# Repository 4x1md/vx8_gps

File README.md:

# DIY GPS Module for Yaesu VX-8DR/VX-8DE Handheld Transceiver
GPS module for Yaesu VX-8DR/DE handheld transceivers with ublox NEO-6M chip and Arduino Nano by Dmitry Melnichansky 4Z7DTF (~~4X5DM since June 2016~~ 4X1MD since July 24, 2017).

## Overview

When I was buying my Yaesu VX-8DE, I knew that I wasn't going to buy the original Yaesu FGPS2 module. There is very little APRS coverage in Israel and APRS in general seemed quite useless to me. The unreasonably high price of the original module didn't make me want to try it either.

After receiving far APRS stations during a strong tropo over the Mediterranean I thought it would be nice to transmit some data. I started investigating how GPS transmits data and discovered the NMEA protocol I had never encountered before. My first source of information was the article [Reverse Engineering the Yaesu VX-8DR GPS Interface](http://lingnik.com/2013/02/09/reverse-engineering-yaesu-vx-8dr-gps-interface.html) by Taylor J Meek KG7BBG.

I started from writing a Python program which was sending NMEA sentences to the transceiver. After some research I discovered the required message format and wrote a program which drew flowers on APRS map.

Later, [David Fannin's project](https://github.com/dfannin/arduino-vx8r-gps) inspired me to build my own GPS module. Thanks to his project I found out the ublox NEO-6M chip and a simple search on AliExpress showed that a ready module can be puchased for $10-20.

I wrote my own software which isn't based on David Fannin's code. I started it as Arduino project but after finding out that the standard Arduino Serial library doesn't support interrupt driven writing and reading I decided to write it in pure C. After small changes the C code can be compiled in Arduino environment. The Arduino code is located in [/arduino/vx8_gps_16mhz folder](https://github.com/4x5dm/vx8_gps/blob/master/arduino/vx8_gps_16mhz) of this repository.

I tried to document this project as much as possible and I hope it will be interesting and useful for other radio amateurs.

## Yaesu VX-8DR/DE and NMEA protocol
The NMEA protocol is implemented in the VX-8 in a non-standard way. There are two main issues with it: serial port parameters and NMEA sentence format. There is also a data validation issue which is very interesting but less important in this case.

### Port parameters: baud rate and logic levels
The original Yaesu FGPS2 module transmits at 9600 bps instead of the standard 4800 bps and uses 3.3V logic level instead of the standard 5V. This isn't a big issue because there are GPS modules which can be configured to transmit at 9600 bps and logic levels can be converted. The GY-GPS6MV2 module came already pre-configured to 9600 bps rate. The ublox NEO-6M chip used in this module has maximum supply voltage of 3.6V. As we see there are no electrical compatibility issues at all.
### NMEA sentence format: field lengths
VX-8 requires all the fields of the NMEA sentence to be padded to the maximum possible number of symbols while regular NMEA standart allows fields to be empty. It means that if there is no GPS fix, typical GGA message will have the following form:
```
$GPGGA,074222.000,,,,,0,00,99.9,,,,,,0000*6E
```
The radio won't be able to process this message and we'll see gibberish on the display. A correct sentence for this transceiver should have the following format:
```
$GPGGA,200124.000,0000.0000,N,00000.0000,E,0,00,00.0,00000.0,M,0000.0,M,000.0,0000*46
```
Sending a sentence with empty fields will result in gibberish on the GPS screen of VX-8. Here is what we'll get.

Allthough the sentence accords with the standard, the transceiver isn't able to process it correctly.

Actually setting number of sybols in each field is what all this project is about! If the second issue didn't exist we could connect the ublox NEO-6M chip based module directly to the transceiver.

### NMEA data validation
Here the things get even more interesting. Yaesu VX-8 does no validation on the NMEA data. When I say no validation, I mean **no validation at all**! Let's look at the following NMEA sentence.
```
$GPGGA,999999.000,73DE.0000,!,Z7DTF.NOPQ,4,1,04
```
The time in the first field is invalid, the latitude and longitude fields have letters instead of numbers, the North/South and East/West fields have invalid characters as well. The checksum is missing. Should it be thrown away by the receiving device? Yes, sure! But let's see how VX-8 will respond!

Have you ever thought about writing some text on the display of your VX-8? Or maybe about setting the time to 89:91:75? Now you know how to do it!

Let's try one more example where there will be no numbers in latitude and longitude fields.
```
$GPGGA,999999.000,ello.ABCD,H,itHub.ABCD,G,1,04
```
And the output is:

Note that last two fields of our so called NMEA sentence mean that there was a valid GPS fix and that it was acquired from 4 satellites. This is exactly what we see on the display: satellites icon with number 4 under it.  This is enough for the transceiver to enable APRS beacon transmission. If you press the internet (TX PO) key these coordinates will be transmitted. Obviously, APRS site will mark such packet as invalid.

When I told you that there is no data validation I really meant no validation at all! You don't even have to add checksum as it will be completely ignored by the radio.

If you want to try it your self you'll need a standard programming cable (original or one from AliExpress) and a terminal program. I used [PuTTY](http://www.putty.org/). Open a new session, choose the correct serial port, set it to 9600 8N1 and you are ready to go. Right mouse click in the terminal window pastes the message from the clipboard. After pasting your message press CTRL+M and then CTRL+J. It will send the CR and LF (ASCII 13 and 10) symbols which mark the end of NMEA sentence.

## Hardware

The hardware is quite simple. GY-GPS6MV2 GPS module transmits its data to the Arduino which does necessary processing and sends it to the transceiver. Allthough the communication between the original Yaesu FGPS2 module and the radio is bi-directional, in my project I decided to make it unidirectional from GPS to radio. Not only is the bi-directional communication useless in this case but also requires one more serial port. This configuration uses only one serial port to communicate with both devices.

Important! The serial port on the Arduino board is also used for programming the device. Leaving the GPS connected to the serial RX pin will cause a conflict and make uploading the firmware impossible. That's why there is a switch which disconnects GPS output from serial input.

On the contrary, using USB serial when the transceiver is connected not only is possible but also is recommended for debugging purposes. You can use any terminal program to monitor Arduino's output even when the radio is connected.

Voltage divider formed by 240 Ohm and 470 Ohm resistors converts the logic levels from 5V used by Arduino to 3.3V required by the transceiver. Two two-color LEDs are used for indication. The left one blinks red if a GGA message was rejected and green if it was sent to the radio. The right one does the same for RMC messages.

All the setup is very similar to [David Fannin's GPS project](https://github.com/dfannin/arduino-vx8r-gps). Main difference is that his project implements bi-directional communication using software serial port emulation for the second port.

The GY-GPS6MV2 GPS recevier and the Arduino Nano clone were both purchases on AliExpress for less than $15.

## Software

To be completed...

## Development history

### First protoype: Arduino Nano and u-blox NEO-6M

The first version was built with readily available modules on a prototype PCB.

### PCB v1.0

The first prototype was built on a dedicated PCB with a standalone ATmega328P-20PU microcontroller in 28 pin DIP package. The PCB was produced at home.

Refer to [prototype_v1.0.md](https://github.com/4x5dm/vx8_gps/blob/master/docs/prototype_v1.0.md) for details.

### PCB v2.0

This version has a USB-to-UART IC which allows the GPS to be used as a programming cable. It was designed as a two-side PCB with SMD parts. Allthough I developed the schematics and the PCB, this version was never built.

The circuit diagram of this version can be found [here](https://raw.githubusercontent.com/4x5dm/vx8_gps/master/docs/images/vx8_gps_prototype_v2.0_schematic.png). Design files are located [here](https://github.com/4x1md/vx8_gps/tree/master/pcbs/vx8_gps_prototype_v2.0).

### PCB v3.0

This version was built on a two-layer PCB. Most parts including ATmega328P microcontroller and the GPS module are SMD. The size of this PCB is 43.5x43.5mm and it was designed to fit a small plastic enclosure box.

Refer to [prototype_v3.0.md](https://github.com/4x5dm/vx8_gps/blob/master/docs/prototype_v3.0.md) for details.

## Field tests

The unit was tested in trains. Videos from the tests are available.

1. [Test 1: Herzliya station](http://www.youtube.com/watch?v=POHEborbWdw)
2. [Test 2: Kiryat Gat station](https://www.youtube.com/watch?v=_s_EKdAwrpI)

## Plans for future development

1. [x] ~~Running all the system at 3.3V.~~ See [prototype_v1.0.md](https://github.com/4x5dm/vx8_gps/blob/master/docs/prototype_v1.0.md) for details.
2. [x] ~~Reducing the microcontroller speed to 8MHz or even lower.~~ See [Release v1.0](https://github.com/4x5dm/vx8_gps/releases/tag/v1.0) ([commit 9e8273a](https://github.com/4x5dm/vx8_gps/commit/9e8273abed9b53197791b6e432649a282e6ca909)) .
3. [ ] Adding a rechargeable battery and making the device USB chargeable.
4. [x] ~~Building the project on a PCB instead of using ready modules.~~
5. [x] ~~Assembling the device in one enclosure box.~~
6. [ ] Making the module compatible with Nikon DSLRs.

Optional/questionable features:

1. [ ] USB serial chip to use the device as a programming cable.
2. [ ] microSD card slot and keeping logs of the tracks.
3. [ ] LCD display for displaying current GPS data.

## Links
1. [Reverse Engineering the Yaesu VX-8DR GPS Interface](http://lingnik.com/2013/02/09/reverse-engineering-yaesu-vx-8dr-gps-interface.html)
2. [FGPS2 data samples (VX-8R Yahoo Group)](https://groups.yahoo.com/neo/groups/VX_8R/conversations/topics/7719)
3. [David Fannin's Yaesu VX-8R Handheld Transmitter-compatible GPS](https://github.com/dfannin/arduino-vx8r-gps)
4. [NMEA to Yaesu VX-8 by G7UHN](http://alloutput.com/amateur-radio/nmea-to-yaesu-vx-8/)
5. [VX-8DR and GPS by VK3YY](https://vk3yy.wordpress.com/2015/07/24/vx-8dr-and-gps/)
6. [GPS - NMEA sentence information](http://aprs.gids.nl/nmea/)
7. [MTK NMEA checksum calculator](http://www.hhhh.org/wiml/proj/nmeaxor.html)
8. [avr-libc 2.0.0: <avr/interrupt.h>: Interrupts](http://www.nongnu.org/avr-libc/user-manual/group__avr__interrupts.html)

## Questions? Suggestions?
You are more than welcome to contact me with any questions, suggestions or propositions regarding this project. You can:

1. Visit [my QRZ.COM page](https://www.qrz.com/db/4X5DM)
2. Visit [my Facebook profile](https://www.facebook.com/Dima.Meln)
3. Write me an email to iosaaris =at= gmail dot com

## How to Support or Say Thanks

If you like this project, or found here some useful information and want to say thanks, or encourage me to do more, you can buy me a coffee!

You can aslo make a donation with PayPal:

---

**73 de 4X1MD ex 4X5DM ex 4Z7DTF**

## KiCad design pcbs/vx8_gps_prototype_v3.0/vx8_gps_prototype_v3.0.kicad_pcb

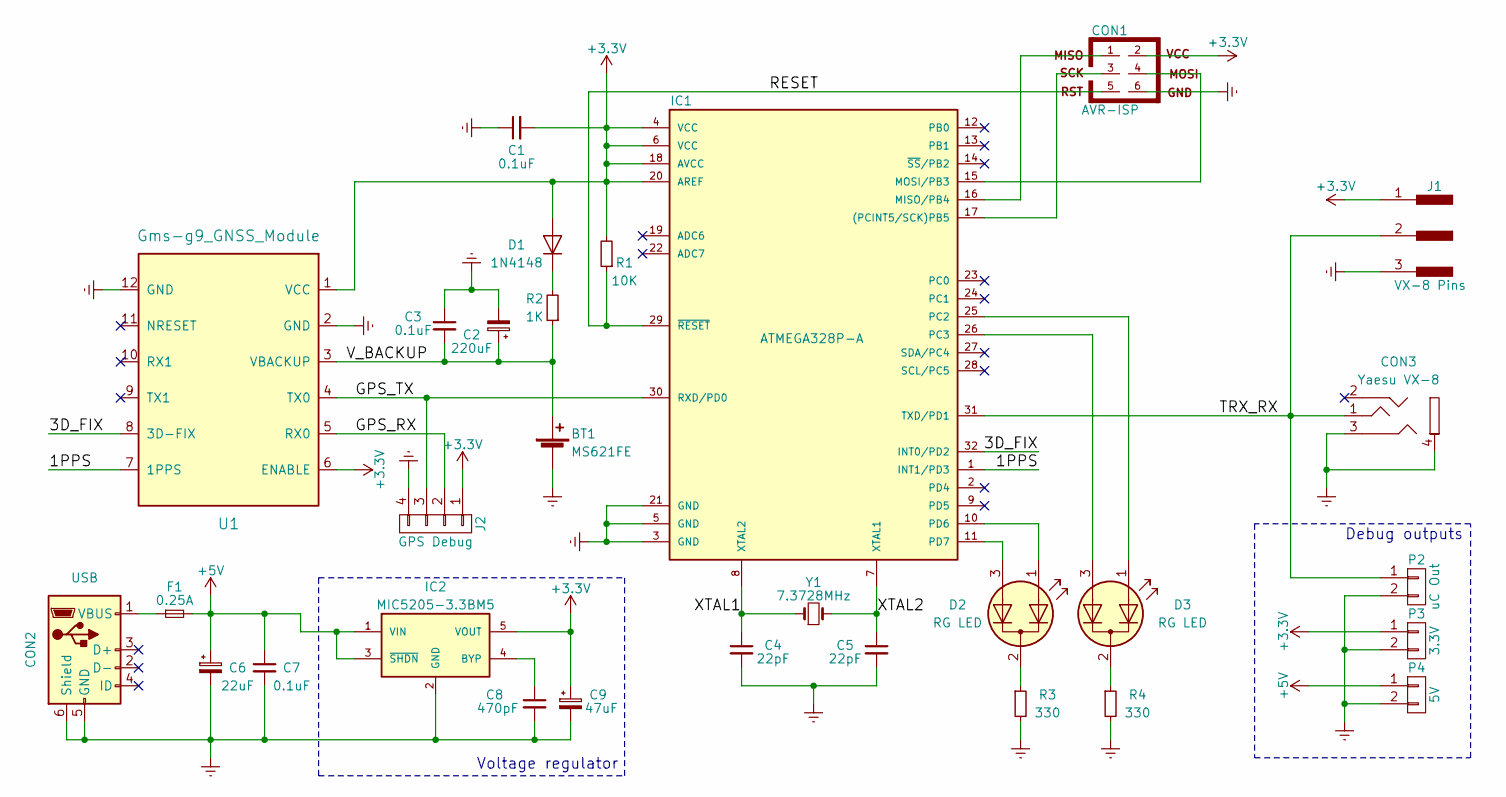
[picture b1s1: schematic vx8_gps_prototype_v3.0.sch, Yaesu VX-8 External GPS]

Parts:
BT1: MS621FE; Seiko_MS621FE-FL11E_Battery
C1, C3, C7: 0.1uF; C_1206
C2: 220uF; CP_Elec_5x5.3
C4, C5: 22pF; C_1206
C6: 22uF; CP_Elec_4x4.5
C8: 470pF; C_1206
C9: 47uF; CP_Elec_4x4.5
CON1: AVR-ISP; Pin_Header_Straight_2x03_Pitch2.54mm
CON2: USB; USB_Mini-B
CON3: Yaesu VX-8; PJ320D_3.5mm_Jack_Short
D1: 1N4148; D_MiniMELF_Standard
D2, D3: RG LED; LED_D3.0mm-3
F1: 0.25A; Fuse_SMD1206_Wave
IC1: ATMEGA328P-A; TQFP-32_7x7mm_Pitch0.8mm
IC2: MIC5205-3.3BM5; SOT-23-5
J1: VX-8 Pins; Connection_Pads_03
J2: GPS Debug; Pin_Header_Straight_1x04_Pitch2.54mm
P2: uC Out; Pin_Header_Straight_1x02_Pitch2.54mm
P3: 3.3V; Pin_Header_Straight_1x02_Pitch2.54mm
P4: 5V; Pin_Header_Straight_1x02_Pitch2.54mm
R1: 10K; R_1206
R2: 1K; R_1206
R3, R4: 330; R_1206
U1: Gms-g9_GNSS_Module
Y1: 7.3728MHz; Crystal_HC49-4H_Vertical

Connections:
+3V3: C1.2, C9.1, CON1.2, D1.2 (A), IC1.4 (VCC), IC1.6 (VCC), IC1.18 (AVCC), IC1.20 (AREF), IC2.5 (VOUT), J1.1, J2.1, P3.1, R1.2, U1.1 (VCC), U1.6 (ENABLE)
+5V: C6.1, C7.1, F1.2, IC2.1 (VIN), IC2.3 (~SHDN~), P4.1
/1PPS: IC1.1 (INT1/PD3), U1.7 (1PPS)
/3D_FIX: IC1.32 (INT0/PD2), U1.8 (3D-FIX)
/GPS_RX: J2.2, U1.5 (RX0)
/GPS_TX: IC1.30 (RXD/PD0), J2.3, U1.4 (TX0)
/RESET: CON1.5, IC1.29 (~RESET~), R1.1
/TRX_RX: CON3.1 (R), IC1.31 (TXD/PD1), J1.2, P2.1
/V_BACKUP: BT1.1 (+), C2.1, C3.2, R2.1, U1.3 (VBACKUP)
/XTAL1: C4.1, IC1.8 (XTAL2), Y1.1
/XTAL2: C5.1, IC1.7 (XTAL1), Y1.2
GNDREF: BT1.2 (-), C1.1, C2.2, C3.1, C4.2, C5.2, C6.2, C7.2, C8.2, C9.2, CON1.6, CON2.5 (GND), CON2.6 (Shield), CON3.3 (GND), CON3.4 (Mic), IC1.3 (GND), IC1.5 (GND), IC1.21 (GND), IC2.2 (GND), J1.3, J2.4, P2.2, P3.2, P4.2, R3.2, R4.2, U1.2 (GND), U1.12 (GND)
unnamed: C8.1, IC2.4 (BYP)
unnamed: CON1.1, IC1.16 (MISO/PB4)
unnamed: CON1.3, IC1.17 ((PCINT5/SCK)PB5)
unnamed: CON1.4, IC1.15 (MOSI/PB3)
unnamed: CON2.1 (VBUS), F1.1
unnamed: D1.1 (K), R2.2
unnamed: D2.1 (A1), IC1.10 (PD6)
unnamed: D2.2 (K), R3.1
unnamed: D2.3 (A2), IC1.11 (PD7)
unnamed: D3.1 (A1), IC1.25 (PC2)
unnamed: D3.2 (K), R4.1
unnamed: D3.3 (A2), IC1.26 (PC3)

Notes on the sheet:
Debug outputs
Voltage regulator

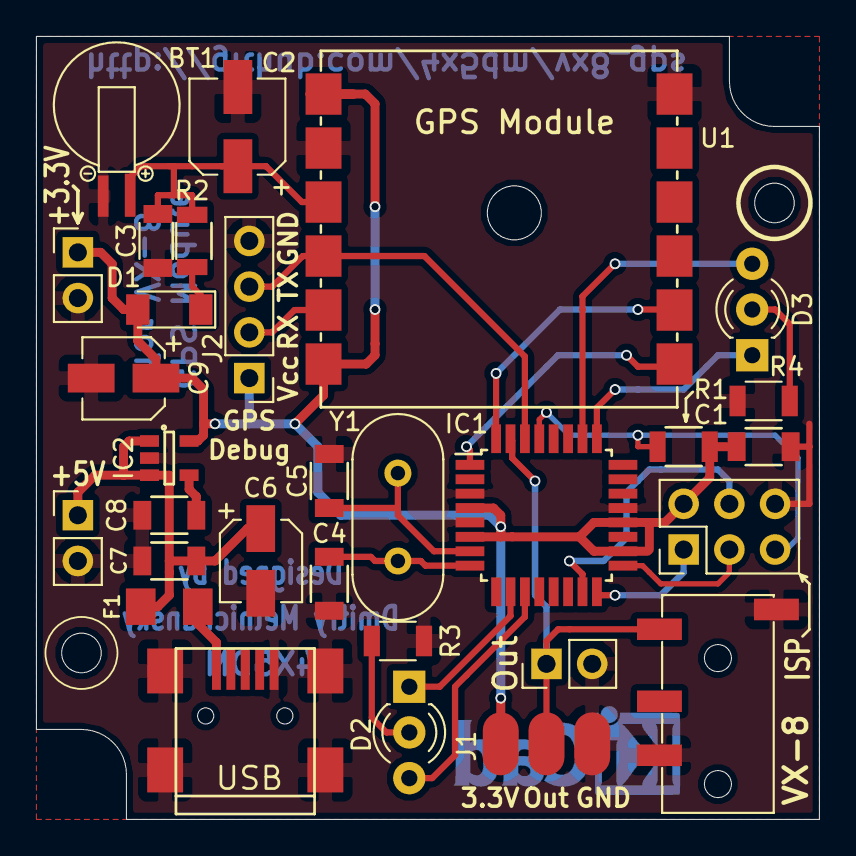
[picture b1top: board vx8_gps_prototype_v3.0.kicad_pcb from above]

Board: 2 copper layers, 43.5 x 43.5 mm, 32 parts (0 on the bottom side), 24 nets.

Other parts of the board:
MH1, MH2: M2; MountingHole_2.2mm_M2

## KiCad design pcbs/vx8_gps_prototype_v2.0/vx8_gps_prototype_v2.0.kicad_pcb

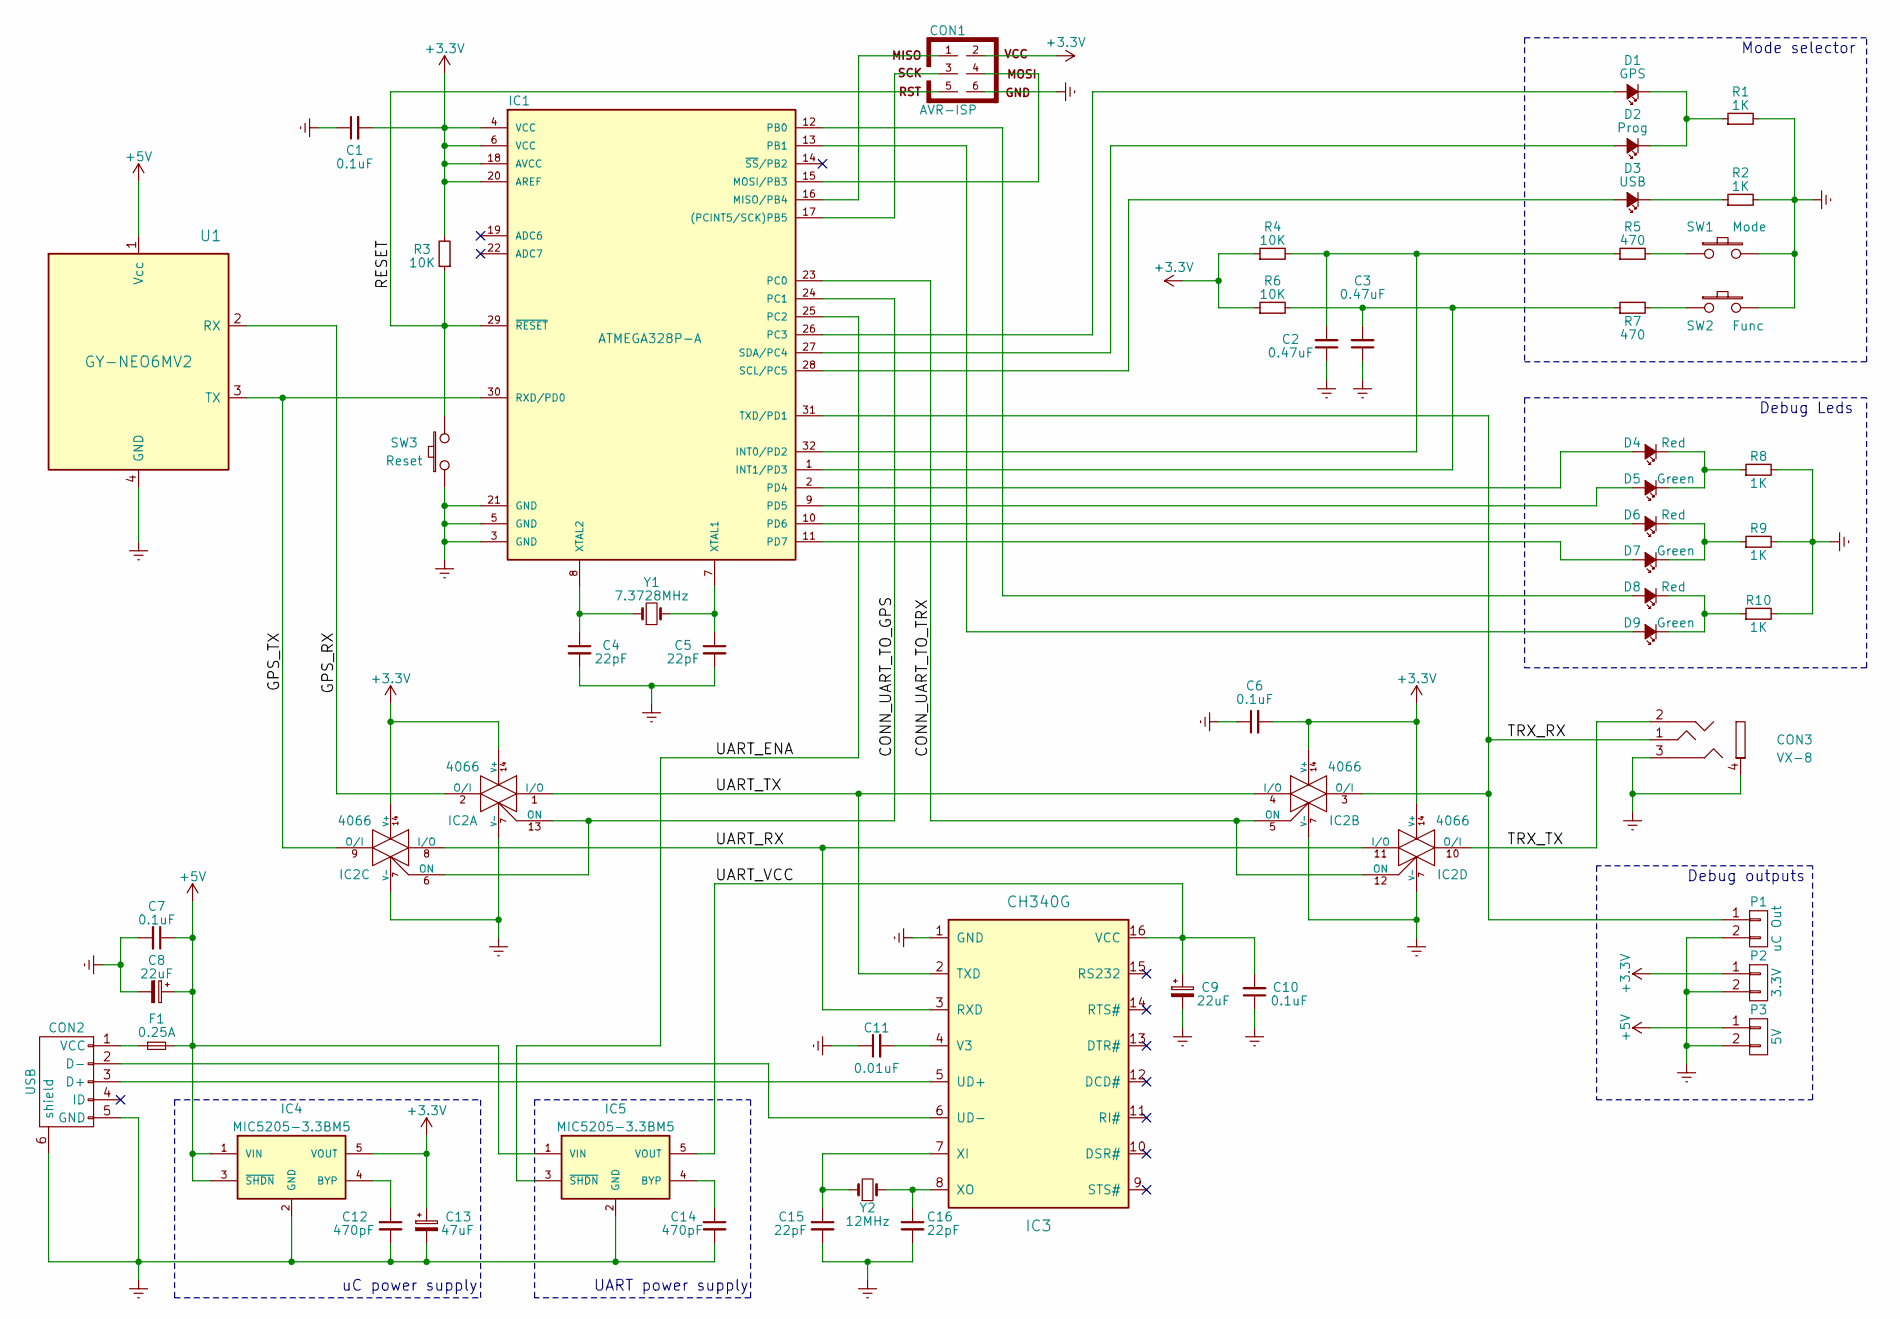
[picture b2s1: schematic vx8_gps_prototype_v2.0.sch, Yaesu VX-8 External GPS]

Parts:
C1, C6, C7, C10: 0.1uF; C_1206
C2, C3: 0.47uF; C_1206
C4, C5, C15, C16: 22pF; C_1206
C8, C9: 22uF; C_Radial_D5_L6_P2.5
C11: 0.01uF; C_1206
C12, C14: 470pF; C_1206
C13: 47uF; C_Radial_D5_L6_P2.5
CON1: AVR-ISP; Pin_Header_Straight_2x03
CON2: USB; USB_Mini-B
CON3: VX-8; PJ320D_3.5mm_Jack
D1: GPS; LED_1206
D2: Prog; LED_1206
D3: USB; LED_1206
D4, D6, D8: Red; LED_1206
D5, D7, D9: Green; LED_1206
F1: 0.25A; Fuse_SMD1206_Wave
IC1: ATMEGA328P-A; TQFP-32_7x7mm_Pitch0.8mm
IC2: 4066; SOIC-14_3.9x8.7mm_Pitch1.27mm
IC3: CH340G; SOIC-16_3.9x9.9mm_Pitch1.27mm
IC4, IC5: MIC5205-3.3BM5; SOT-23-5
P1: uC Out; Pin_Header_Straight_1x02_Pitch2.54mm
P2: 3.3V; Pin_Header_Straight_1x02_Pitch2.54mm
P3: 5V; Pin_Header_Straight_1x02_Pitch2.54mm
R1, R2, R8, R9, R10: 1K; R_1206
R3, R4, R6: 10K; R_1206
R5, R7: 470; R_1206
SW1: Mode; SW_SPST_PTS645
SW2: Func; SW_SPST_PTS645
SW3: Reset; SW_SPST_B3U-1000P
U1: GY-NEO6MV2; GY-NEO6MV2_GPS
Y1: 7.3728MHz; HC-49V
Y2: 12MHz; Q_49U3HMS

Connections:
+3V3: C1.2, C6.2, C13.1, CON1.2, IC1.4 (VCC), IC1.6 (VCC), IC1.18 (AVCC), IC1.20 (AREF), IC2.14 (V+), IC4.5 (VOUT), P2.1, R3.2, R4.1, R6.1
+5V: C7.1, C8.1, F1.2, IC4.1 (VIN), IC4.3 (~SHDN~), IC5.1 (VIN), P3.1, U1.1 (Vcc)
/CONN_UART_TO_GPS: IC1.24 (PC1), IC2.6 (ON), IC2.13 (ON)
/CONN_UART_TO_TRX: IC1.23 (PC0), IC2.5 (ON), IC2.12 (ON)
/GPS_RX: IC2.2 (O/I), U1.2 (RX)
/GPS_TX: IC1.30 (RXD/PD0), IC2.9 (O/I), U1.3 (TX)
/RESET: CON1.5, IC1.29 (~RESET~), R3.1, SW3.2
/TRX_RX: CON3.1 (R), IC1.31 (TXD/PD1), IC2.3 (O/I), P1.1
/TRX_TX: CON3.2 (L), IC2.10 (O/I)
/UART_ENA: IC1.25 (PC2), IC5.3 (~SHDN~)
/UART_RX: IC2.8 (I/O), IC2.11 (I/O), IC3.3 (RXD)
/UART_TX: IC2.1 (I/O), IC2.4 (I/O), IC3.2 (TXD)
/UART_VCC: C9.1, C10.2, IC3.16 (VCC), IC5.5 (VOUT)
GNDREF: C1.1, C2.1, C3.1, C4.2, C5.2, C6.1, C7.2, C8.2, C9.2, C10.1, C11.1, C12.2, C13.2, C14.2, C15.2, C16.2, CON1.6, CON2.5 (GND), CON2.6 (shield), CON3.3 (GND), CON3.4 (Mic), IC1.3 (GND), IC1.5 (GND), IC1.21 (GND), IC2.7 (V-), IC3.1 (GND), IC4.2 (GND), IC5.2 (GND), P1.2, P2.2, P3.2, R1.2, R2.2, R8.2, R9.2, R10.2, SW1.2, SW2.2, SW3.1, U1.4 (GND)
unnamed: C2.2, IC1.32 (INT0/PD2), R4.2, R5.1
unnamed: C3.2, IC1.1 (INT1/PD3), R6.2, R7.1
unnamed: C4.1, IC1.8 (XTAL2), Y1.1
unnamed: C5.1, IC1.7 (XTAL1), Y1.2
unnamed: C11.2, IC3.4 (V3)
unnamed: C12.1, IC4.4 (BYP)
unnamed: C14.1, IC5.4 (BYP)
unnamed: C15.1, IC3.7 (XI), Y2.1
unnamed: C16.1, IC3.8 (XO), Y2.2
unnamed: CON1.1, IC1.16 (MISO/PB4)
unnamed: CON1.3, IC1.17 ((PCINT5/SCK)PB5)
unnamed: CON1.4, IC1.15 (MOSI/PB3)
unnamed: CON2.1 (VCC), F1.1
unnamed: CON2.2 (D-), IC3.6 (UD-)
unnamed: CON2.3 (D+), IC3.5 (UD+)
unnamed: D1.1 (K), D2.1 (K), R1.1
unnamed: D1.2 (A), IC1.26 (PC3)
unnamed: D2.2 (A), IC1.27 (SDA/PC4)
unnamed: D3.1 (K), R2.1
unnamed: D3.2 (A), IC1.28 (SCL/PC5)
unnamed: D4.1 (K), D5.1 (K), R8.1
unnamed: D4.2 (A), IC1.2 (PD4)
unnamed: D5.2 (A), IC1.9 (PD5)
unnamed: D6.1 (K), D7.1 (K), R9.1
unnamed: D6.2 (A), IC1.10 (PD6)
unnamed: D7.2 (A), IC1.11 (PD7)
unnamed: D8.1 (K), D9.1 (K), R10.1
unnamed: D8.2 (A), IC1.12 (PB0)
unnamed: D9.2 (A), IC1.13 (PB1)
unnamed: R5.2, SW1.1
unnamed: R7.2, SW2.1

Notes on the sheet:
Debug outputs
Debug Leds
Mode selector
uC power supply
UART power supply

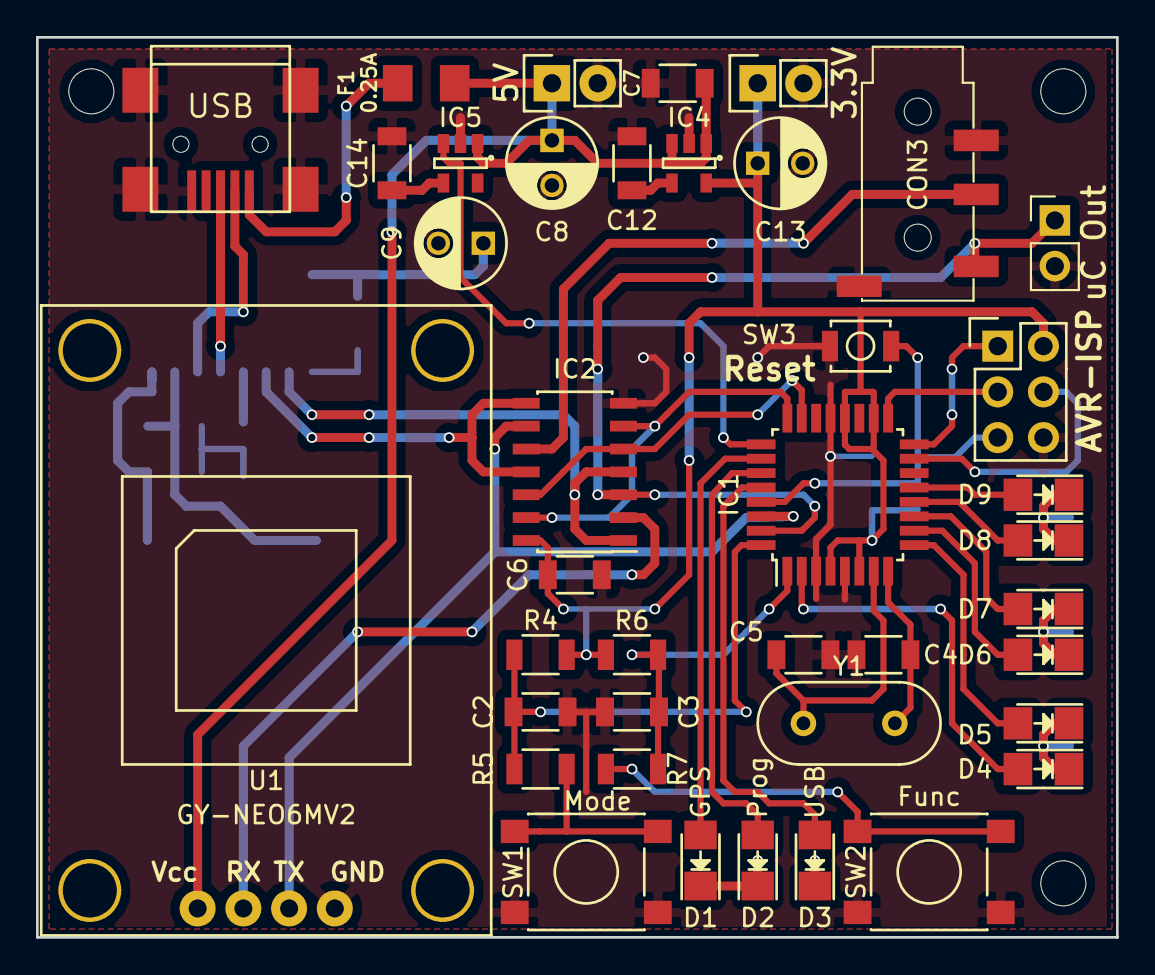
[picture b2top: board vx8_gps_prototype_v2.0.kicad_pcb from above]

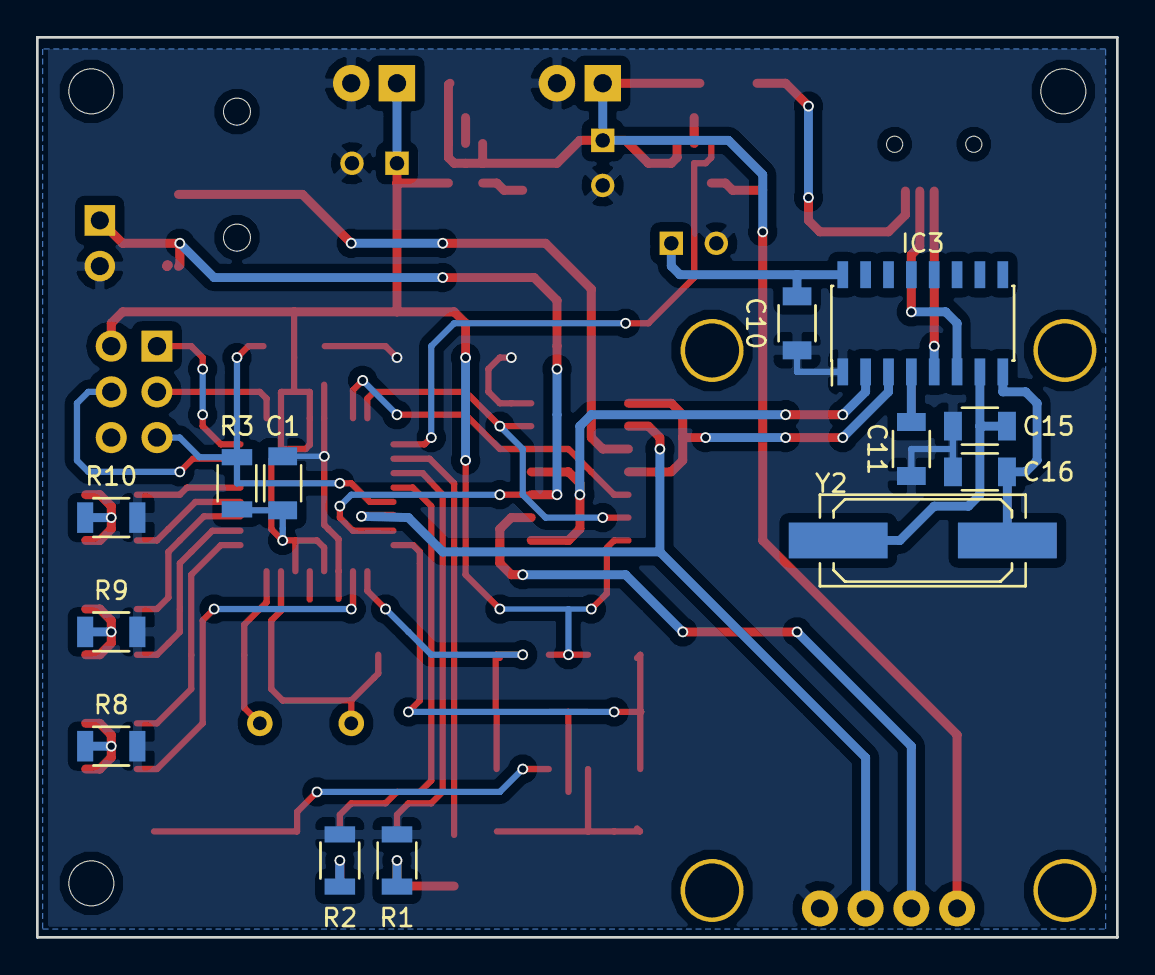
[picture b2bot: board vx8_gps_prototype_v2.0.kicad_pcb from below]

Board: 2 copper layers, 60.0 x 50.0 mm, 56 parts (13 on the bottom side), 45 nets.

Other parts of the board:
MH1, MH3, MH4: 2.5mm; MountingHole_2.5mm

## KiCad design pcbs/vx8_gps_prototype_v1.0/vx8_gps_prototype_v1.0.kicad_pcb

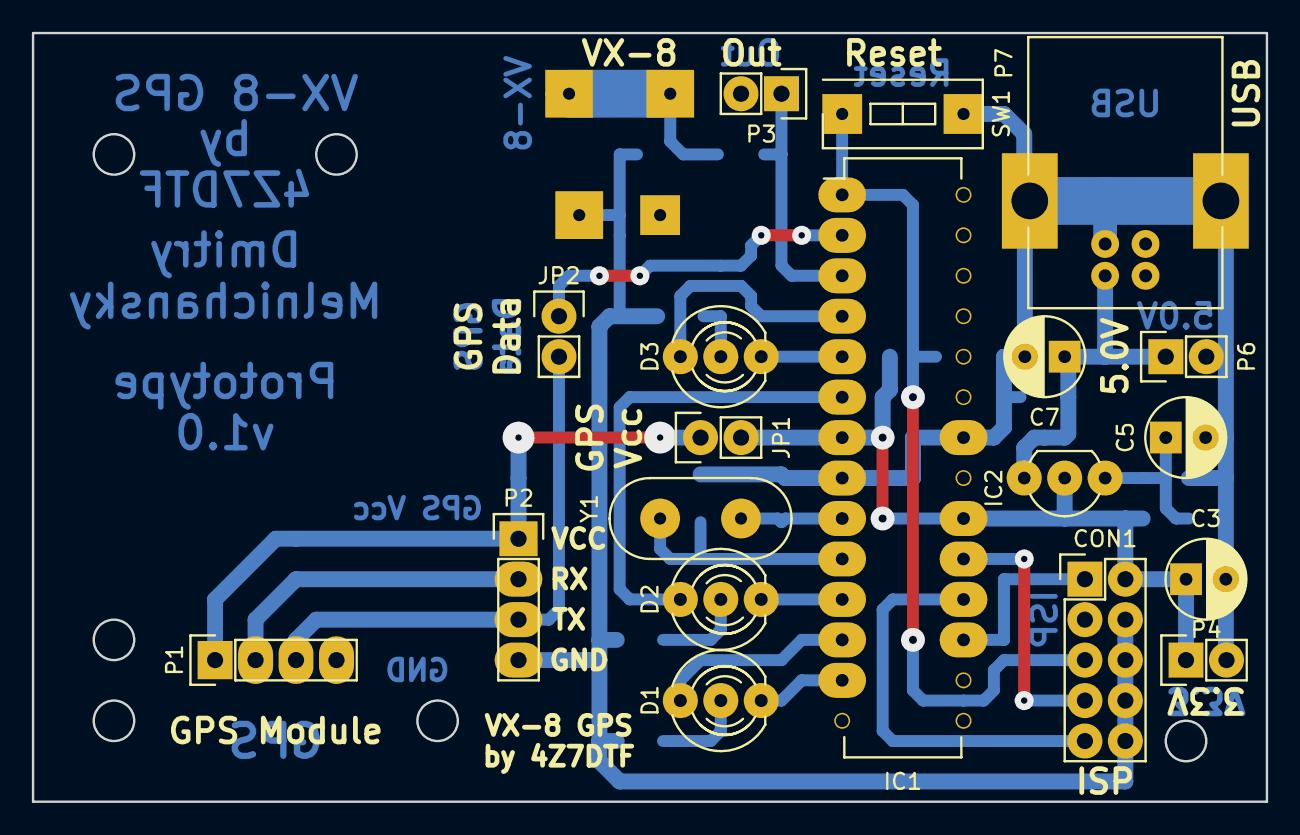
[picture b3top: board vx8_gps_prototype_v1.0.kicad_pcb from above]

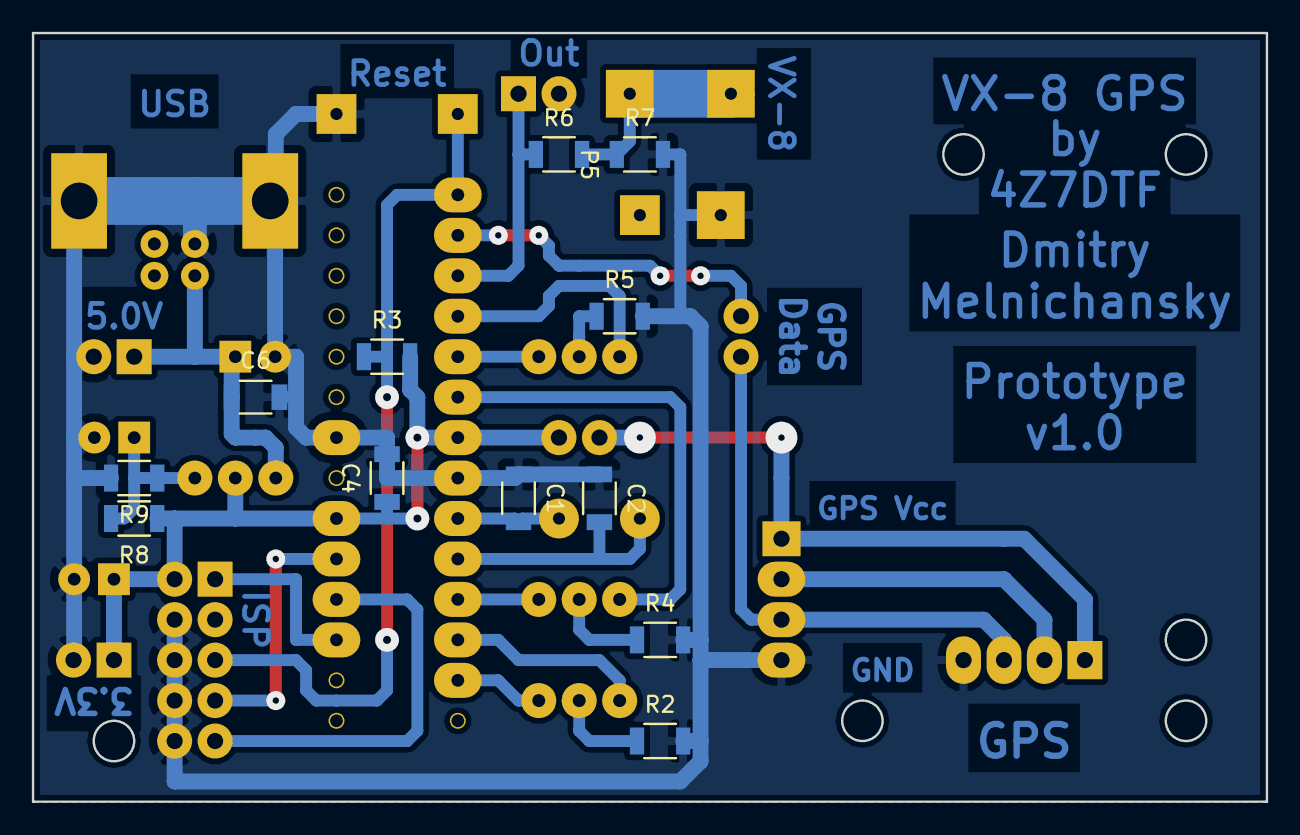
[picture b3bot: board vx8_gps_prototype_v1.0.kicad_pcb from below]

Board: 2 copper layers, 77.5 x 48.3 mm, 32 parts (13 on the bottom side), 25 nets.

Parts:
C1, C2: 22pF; C_1206
C3, C5: 10uF; C_Radial_D5_L11_P2.5
C4, C6: 0.1uF; C_1206
C7: 47uF; C_Radial_D5_L11_P2.5
CON1: AVR-ISP-10; Pin_Header_Straight_2x05
D1, D2, D3: RG Led; LED-5MM-3
IC1: ATMEGA328P-P; DIP-28_W7.62mm_LongPads
IC2: LM317T; TO-92_Inline_Wide
JP1: GPS Vcc; Pin_Header_Straight_1x02
JP2: GPS Data; Pin_Header_Straight_1x02
P1: GY-GPS6MV2; Pin_Header_Straight_1x04
P2: GPS Ser.; Pin_Header_Straight_1x04
P3: Out; Pin_Header_Straight_1x02
P4: 3.3V; Pin_Header_Straight_1x02
P5: VX-8; 3.5mm_Jack
P6: 5V; Pin_Header_Straight_1x02
P7: USB B; USB_B
R2, R4, R5: 560; R_1206
R3: 10K; R_1206
R6, R8: 240; R_1206
R7: 470; R_1206
R9: 390; R_1206
SW1: Reset; SW_DIP_x1_Slide
Y1: 4MHz; HC-49V

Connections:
/RX: P1.2, P2.2
/TX: JP2.2, P1.3, P2.3
/Vcc: JP1.1, P1.1, P2.1
GNDREF: C1.1, C2.1, C3.2, C4.2, C5.2, C6.2, C7.2, CON1.4, CON1.6, CON1.8, CON1.10, IC1.8, IC1.22, P1.4, P2.4, P3.2, P4.2, P5.3, P6.2, P7.4, P7.5, R2.2, R4.2, R5.2, R7.2, R9.2, SW1.2
unnamed: C1.2, IC1.9, Y1.2
unnamed: C2.2, IC1.10, Y1.1
unnamed: C3.1, C4.1, CON1.2, IC1.7, IC1.20, IC2.2, JP1.2, P4.1, R3.2, R8.1
unnamed: C5.1, IC2.1, R8.2, R9.1
unnamed: C6.1, C7.1, IC2.3, P6.1, P7.1
unnamed: CON1.1, IC1.17
unnamed: CON1.5, IC1.1, R3.1, SW1.1
unnamed: CON1.7, IC1.19
unnamed: CON1.9, IC1.18
unnamed: D1.1, IC1.13
unnamed: D1.2, R2.1
unnamed: D1.3, IC1.12
unnamed: D2.1, IC1.11
unnamed: D2.2, R4.1
unnamed: D2.3, IC1.6
unnamed: D3.1, IC1.5
unnamed: D3.2, R5.1
unnamed: D3.3, IC1.4
unnamed: IC1.2, JP2.1
unnamed: IC1.3, P3.1, R6.1
unnamed: P5.1, R6.2, R7.1

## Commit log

2016-01-10 Connections diagram.
2016-01-10 GPS strings with fix and without.
2016-01-10 Program code.
2016-01-10 Binary file for uploading to Arduino.
2016-01-10 Yaesu VX8 images.
2016-01-10 Images
2016-01-11 Led pins.
2016-01-16 APRS flower.
2016-01-16 Arduino version.
2016-03-20 Arduino code. Tested with Arduino Nano 16MHz on 20 March 2016.
2016-03-20 README.md
2016-03-20 New directory structure.
2016-03-25 Led output pin deifinitions.
2016-03-26 Updated Arduino code and hex file.
2016-03-26 Folders structure.
2016-03-26 Prototype v1.0: KiCAD files.
2016-03-26 Prototype v1.0: description & photos.
2016-03-28 1. #define directives for constants. 2. Changed str_len() function in str_func.c. 3. Arduino code uses TX complete interrupt instead of UDR0 empty interrupt.
2016-04-01 1. USART Buffer Empty interrupt used for TX. 2. TX routines removed completely from the main loop. All the transmission is processed in the interrupt service routine. 3. Tested with Arduino Nano at 1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
2016-04-02 1. TX and RX buffers changed to struct. 2. reset_rx() replaced with RESET state.
2016-04-02 Buffer empty vector routine.
2016-04-02 Removed copy_msg_to_tx_buf().
2016-04-02 Removed frac_len() and str_len() functions as not required.
2016-08-20 GY-NEO6MV2 module outline drawing.
2017-04-17 Prototype v2.0.
2017-04-17 Prototype v3.0.
2018-10-01 Minor update.
2020-04-15 Added description about new PCB versions.
